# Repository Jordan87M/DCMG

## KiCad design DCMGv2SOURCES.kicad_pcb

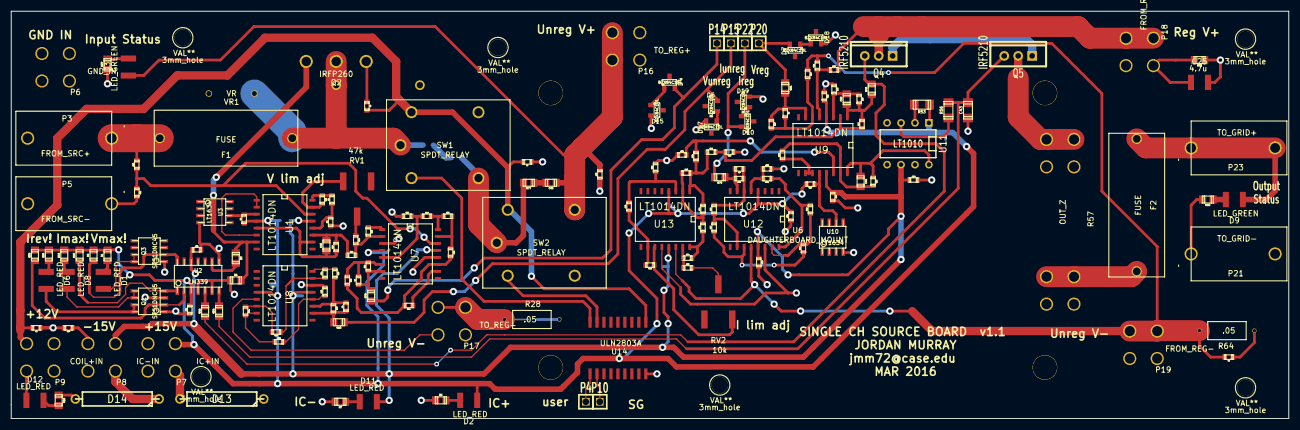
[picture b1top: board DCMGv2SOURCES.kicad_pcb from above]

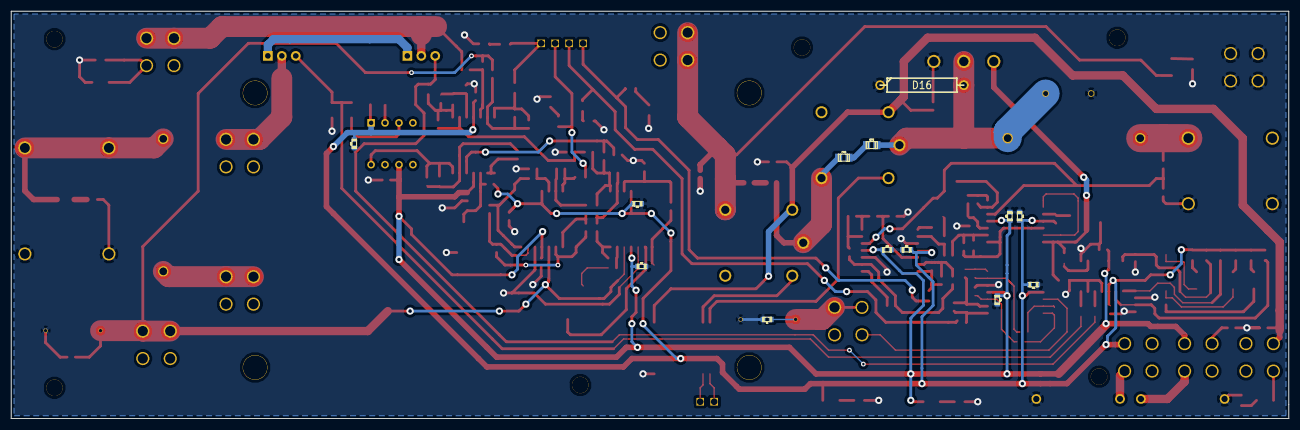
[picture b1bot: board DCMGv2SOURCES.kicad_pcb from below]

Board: 2 copper layers, 232.7 x 74.2 mm, 182 parts (13 on the bottom side), 102 nets.

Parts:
3mm_hole, 3mm_hole#2, 3mm_hole#3, 3mm_hole#4, 3mm_hole#5, 3mm_hole#6: VAL**; 3mm_hole
C1, C2: 10n; c_0603
C3, C4, C5, C9, C10: 2.2n; c_0603
C6, C7, C8: COIL_BYPASS; c_0603
C15, C33, C44: .22u; c_0805
C16: 1u; c_0603
C17, C18, C19, C20, C21, C22, C23, C24, C34, C35, C36, C37, C38, C39, C40, C41, C42: VCC_BYP; c_0603
C25: 4.7u; 1209
C43: 1.2u; c_1206
C45, C46: C; c_0805
D1, D2, D6, D8, D11, D12: LED_RED; 1209
D3, D9: LED_GREEN; 1209
D4, D5, D7, D10, D15, D17, D18, D19: BZX84C10L; SOT23
D13, D14, D16: DIODESCH; R6
F1, F2: FUSE; OMNI-BLOCK
P3: FROM_SRC+; DELTRON BANANA
P4: CTRL_SIG; MOLEX-1
P5: FROM_SRC-; DELTRON BANANA
P6: GND_IN; Screw Terminal 8191
P7: IC+IN; Screw Terminal 8191
P8: IC-IN; Screw Terminal 8191
P9: COIL+IN; Screw Terminal 8191
P10: NC_SCGR_SIG; MOLEX-1
P14: UNREG_V_SIG; MOLEX-1
P15: UNREG_I_SIG; MOLEX-1
P16: TO_REG+; Screw Terminal 8191
P17: TO_REG-; Screw Terminal 8191
P18: FROM_REG+; Screw Terminal 8191
P19: FROM_REG-; Screw Terminal 8191
P20: REG_V_SIG; MOLEX-1
P21: TO_GRID-; DELTRON BANANA
P22: REG_I_SIG; MOLEX-1
P23: TO_GRID+; DELTRON BANANA
Q1, Q3: STS1DNC45; so-8
Q2: IRFP260; TO247
Q4, Q5: IRF5210; TO220_VERT
R1, R6, R7, R10, R27, R36, R46, R62: 2.2k; c_0805
R2, R4, R39, R50: 33k; c_0805
R3, R44, R48, R54, R78, R79, R80, R81: 22; c_0805
R5, R43: 47k; c_0603
R8, R9, R11, R15, R16, R17, R19, R20, R22, R24, R25, R26, R37, R38, R41, R42, R47, R52, R55, R58: 12k; c_0603
R12: 10M; c_0603
R14, R21, R31, R34, R63, R67: 3.3k; c_0603
R18: 33k; c_0603
R23: 15k; c_0603
R28, R64: .05; OHMITE_1W
R29, R32, R61, R66, R70, R73: 5.6k; c_0603
R30, R33, R60, R65, R69, R72: 22k; c_0603
R35, R68, R75: 1.2k; c_0603
R40: MIN_LOAD; c_0805
R45, R49, R51, R59: 470; c_0603
R53: 50; c_1206
R56: 33; c_1206
R57: OUT_Z; Double Terminal 8191
R71, R74: 8.2k; c_0603
R76, R77: R; c_0805
RV1: 47k; Bourns_3361
RV2: 10k; Bourns_3361
SW1, SW2: SPDT_RELAY; OMRON_GL5E-1
U1, U7, U8, U9, U12, U13: LT1014DN; SO16W
U2: LM339; so-14
U3, U10: LT1634; so-8
U6: DAUGHTERBOARD_MOUNT
U11: LT1010; DIP-8__300
U14: ULN2803A; SOIC-18
VR1: VR; MOV-10DxxxK

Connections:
COIL_POW+: C6.1, C7.1, C8.1, D12.1, P9.1, SW1.2, SW2.2, U14.10
CTRL_GND: C1.1, C2.2, C6.2, C7.2, C8.2, C16.2, C17.1, C18.2, C19.1, C20.2, C21.1, C22.2, C23.1, C24.2, C25.2, C34.1, C35.2, C36.1, C37.2, C38.1, C39.2, C40.1, C41.2, C42.1, C43.2, D13.1, D14.2, D15.2, D16.1, D17.2, D18.2, D19.2, P5.1, P6.1, P21.1, Q1.1, Q1.3, Q2.3, Q3.1, R4.2, R6.2, R7.1, R9.2, R10.2, R20.2, R21.1, R27.2, R28.1, R30.1, R40.2, R45.2, R52.2, R58.2, R60.1, R62.1, R64.2, R69.1, U2.4, U2.6, U2.8, U3.4, U7.3, U7.12, U8.14, U10.4, U12.14, U13.12, U14.9, VR1.2
IC_POW+: C18.1, C20.1, C22.1, C24.1, C35.1, C37.1, C39.1, C41.1, D2.1, D13.2, P7.1, R1.1, R2.1, R5.2, R36.1, R39.1, R43.1, R46.1, R50.1, R53.2, U1.4, U2.3, U7.4, U8.4, U9.4, U11.1, U12.4, U13.4
IC_POW-: C17.2, C19.2, C21.2, C23.2, C34.2, C36.2, C38.2, C40.2, C42.2, D11.2, D14.1, P8.1, U1.13, U2.12, U7.13, U8.13, U9.13, U11.6, U12.13, U13.13
unnamed: R19.2, R20.1, U7.5
unnamed: C3.2, R26.2, R78.1, U7.7
unnamed: R22.1, R23.2, U7.15
unnamed: R24.2, U7.10
unnamed: R8.2, R9.1, U1.12
unnamed: C15.1, R16.2, R17.1, U1.11
unnamed: C15.2, R17.2, U1.5, U1.10
unnamed: R18.2, R21.2, U1.14, U7.14
unnamed: R15.2, U7.1
unnamed: R14.2, RV1.2
unnamed: Q1.2, R39.2, U2.2
unnamed: D8.1, R46.2
unnamed: D8.2, Q1.5, Q1.6
unnamed: R54.1, U2.7
unnamed: Q1.4, R50.2, U2.1
unnamed: R3.1, U2.9
unnamed: D6.1, R36.2
unnamed: D6.2, Q1.7, Q1.8
unnamed: R44.1, U2.5
unnamed: D3.2, R27.1
unnamed: C9.2, R65.2, R66.1, U12.6
unnamed: Q3.2, R2.2, U2.14
unnamed: D1.2, Q3.7, Q3.8
unnamed: SW2.9, U14.17
unnamed: P10.1, U14.2
unnamed: SW1.9, U14.18
unnamed: P4.1, U14.1
unnamed: C33.1, R45.1, R47.2, U9.3
unnamed: C33.2, R12.1, R47.1, R48.2, U9.1
unnamed: Q4.2, R44.2, R48.1
unnamed: D4.2, P14.1, R78.2
unnamed: D10.2, P22.1, R79.1
unnamed: D7.2, P20.1, R81.2
unnamed: D5.2, P15.1, R80.2
unnamed: C45.1, R76.2
unnamed: C45.2, R77.1, SW1.10, SW2.5
unnamed: C46.1, R77.2
unnamed: R75.1, RV2.2
unnamed: R69.2, R70.1, U13.3
unnamed: R49.2, U9.10, U9.11
unnamed: R43.2, U9.12, U10.6
unnamed: R12.2, R51.1, R52.1, U9.2
unnamed: R5.1, U1.3, U3.6
unnamed: U1.1, U1.2, U1.6
unnamed: R41.2, R42.2, U9.5
unnamed: D9.2, R62.2
unnamed: Q2.1, R3.2, R4.1, U1.7
unnamed: C44.2, R55.2, U9.16, U11.8
unnamed: C25.1, P18.1, Q4.3, R40.1, R42.1
unnamed: C5.2, R38.2, R81.1, U9.7
unnamed: C5.1, R37.1, R38.1, U9.6
unnamed: C9.1, R65.1, R79.2, U12.7
unnamed: C10.1, R51.2, R59.2, R72.1, U13.1
unnamed: C10.2, R72.2, R73.1, U13.2
unnamed: C3.1, R25.2, R26.1, U7.6
unnamed: C4.2, R33.1, R80.1, U8.10
unnamed: Q5.3, R57.2
unnamed: Q4.1, Q5.1
unnamed: D4.1, D15.1
unnamed: D5.1, D17.1
unnamed: D7.1, D18.1
unnamed: D10.1, D19.1
unnamed: R58.1, R59.1, U9.14
unnamed: C44.1, R49.1, R55.1, U9.15
unnamed: D1.1, R1.2
unnamed: C4.1, R32.1, R33.2, U8.11
unnamed: R29.1, R30.2, U8.12
unnamed: R53.1, U11.2
unnamed: R56.2, U11.3
unnamed: C43.1, Q5.2, R54.2, R56.1
unnamed: R60.2, R61.1, U12.5
unnamed: F2.2, R57.1
unnamed: D9.1, F2.1, P23.1
unnamed: R63.2, R68.1, U12.15
unnamed: R29.2, R31.1, U8.7
unnamed: R31.2, R35.1, U8.6
unnamed: R34.2, R35.2, U8.15
unnamed: R32.2, R34.1, U8.16
unnamed: R61.2, R63.1, U12.16
unnamed: R67.2, R68.2, U12.11
unnamed: R66.2, R67.1, U12.10
unnamed: C16.1, C46.2, D3.1, P16.1, SW2.1
unnamed: D11.1, R7.2
unnamed: D12.2, R10.1
unnamed: D2.2, R6.1
unnamed: C1.2, P17.1, R28.2, U8.5
unnamed: D16.2, F1.1, Q2.2, R76.1, SW1.5, VR1.1
unnamed: F1.2, P3.1, R18.1
unnamed: C2.1, P19.1, R37.2, R41.1, R64.1, U12.12, U13.14
unnamed: R19.1, R22.2, U7.16
unnamed: R23.1, R24.1, R25.1, U7.11
unnamed: R71.2, RV2.3, U13.11
unnamed: R70.2, R71.1, U13.10
unnamed: R74.2, R75.2, U13.15
unnamed: R73.2, R74.1, U13.16
unnamed: R14.1, R15.1, R16.1, U7.2
unnamed: R8.1, R11.2, U1.16
unnamed: R11.1, RV1.3, U1.15

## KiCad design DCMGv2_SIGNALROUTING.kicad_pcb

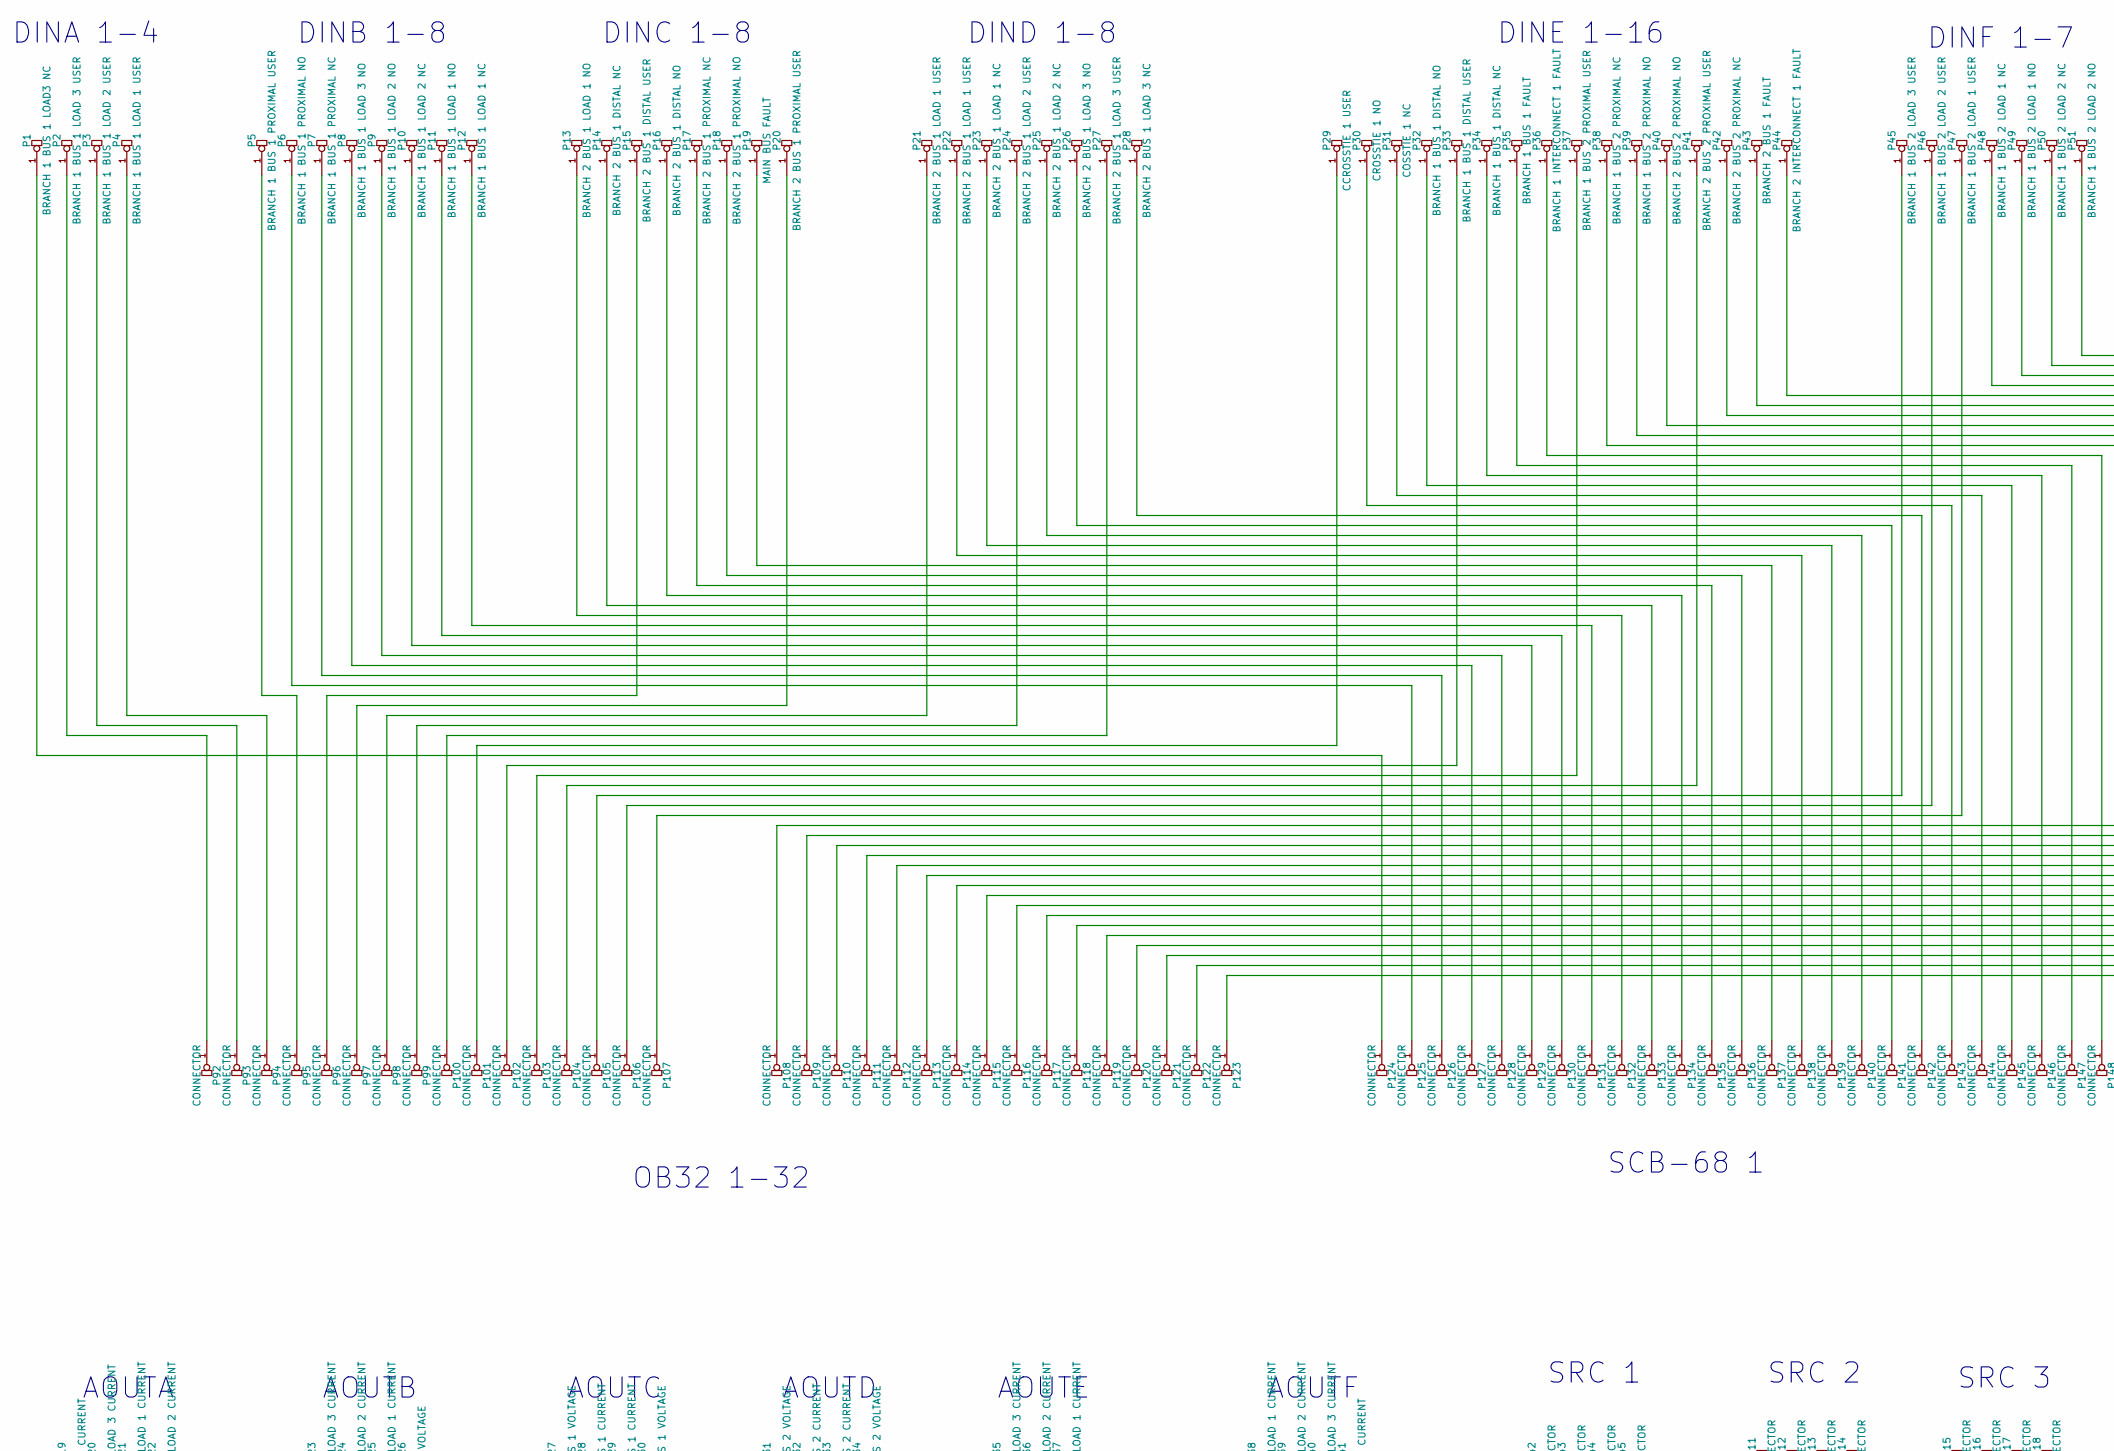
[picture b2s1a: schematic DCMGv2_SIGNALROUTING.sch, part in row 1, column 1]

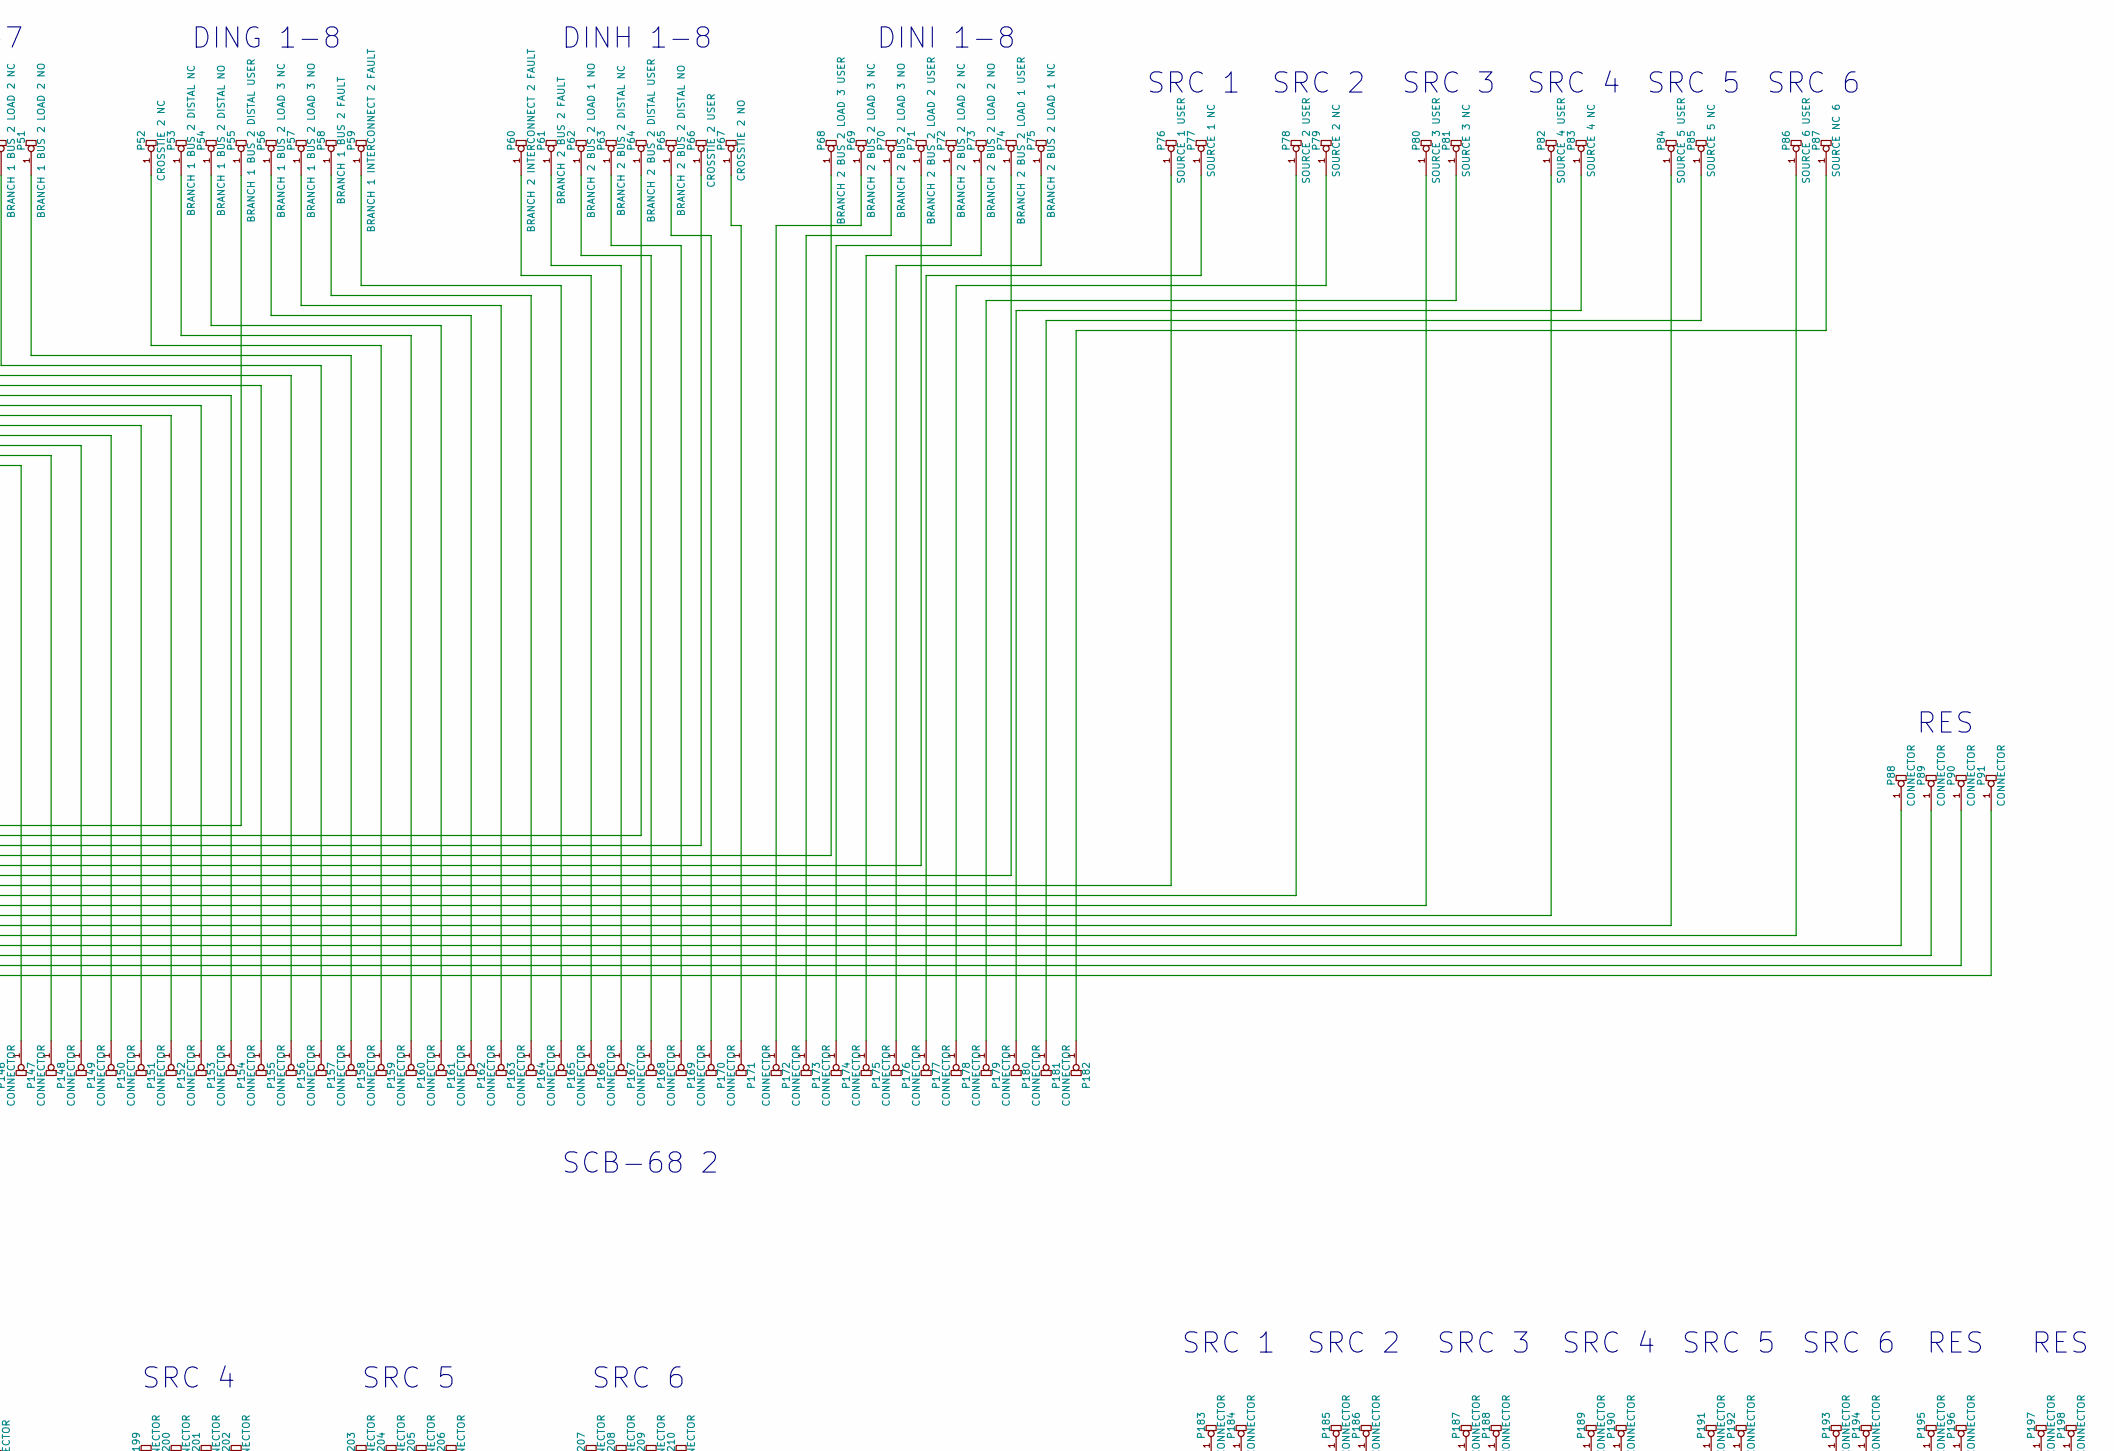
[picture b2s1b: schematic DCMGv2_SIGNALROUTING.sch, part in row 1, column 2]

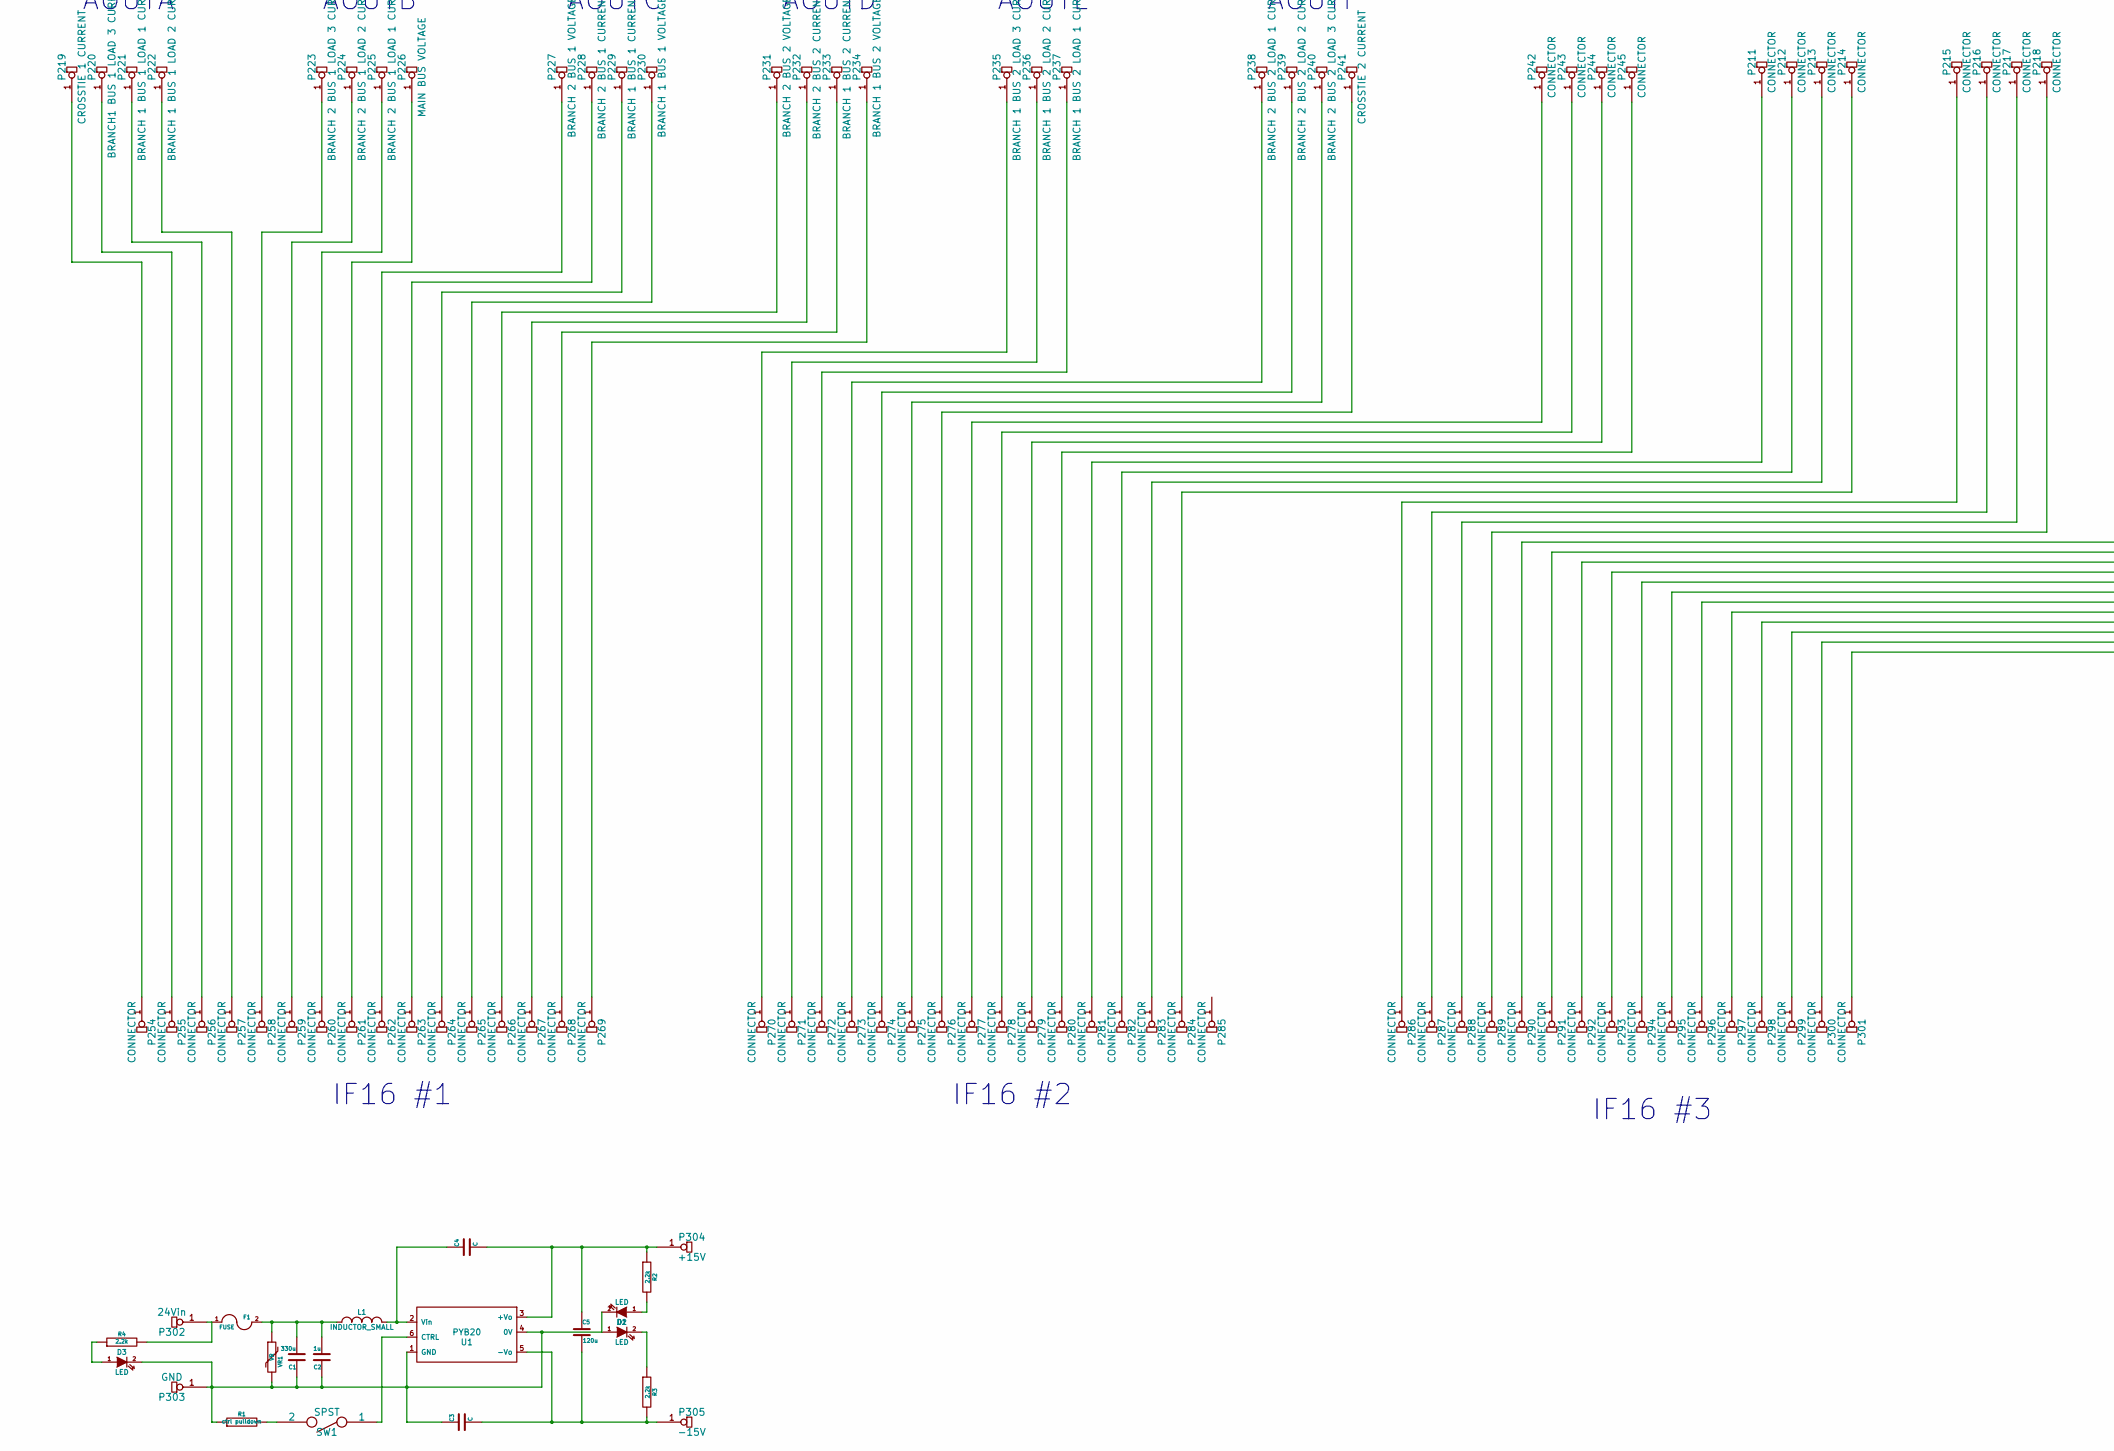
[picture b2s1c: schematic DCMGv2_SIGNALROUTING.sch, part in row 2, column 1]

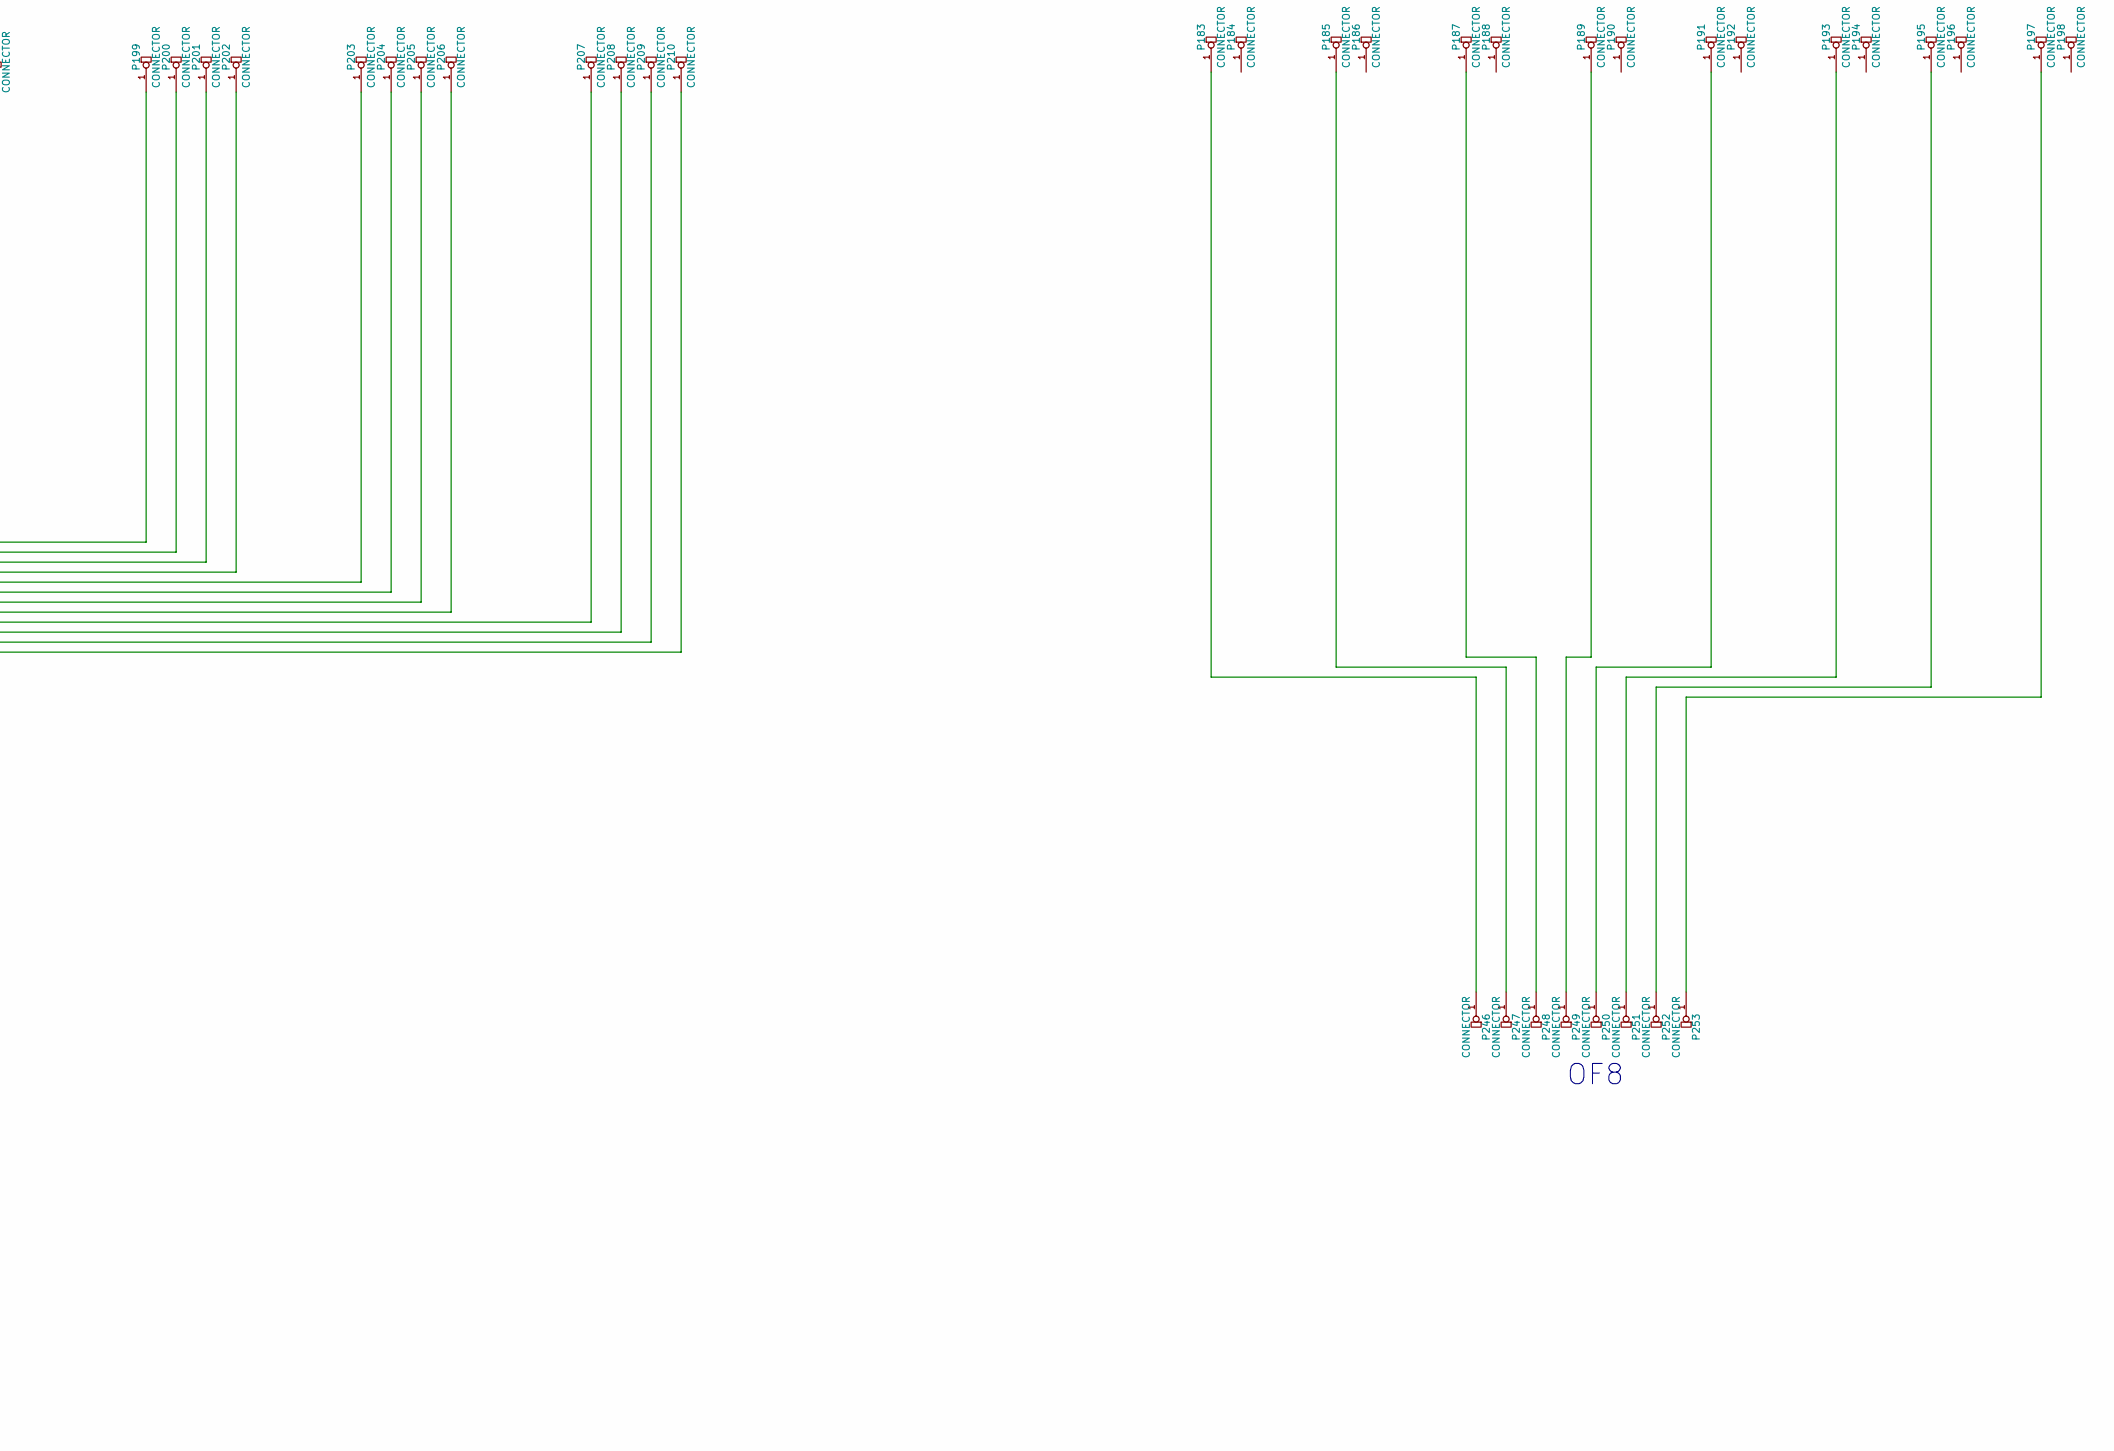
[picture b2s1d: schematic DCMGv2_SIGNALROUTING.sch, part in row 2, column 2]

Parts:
C1: 330u
C2: 1u
C3, C4: C
C5: 120u
D1, D2, D3: LED
F1: FUSE
L1: INDUCTOR_SMALL
P1: BRANCH 1 BUS 1 LOAD3 NC
P2: BRANCH 1 BUS 1 LOAD 3 USER
P3: BRANCH 1 BUS 1 LOAD 2 USER
P4: BRANCH 1 BUS 1 LOAD 1 USER
P5: BRANCH 1 BUS 1 PROXIMAL USER
P6: BRANCH 1 BUS 1 PROXIMAL NO
P7: BRANCH 1 BUS 1 PROXIMAL NC
P8: BRANCH 1 BUS 1 LOAD 3 NO
P9: BRANCH 1 BUS 1 LOAD 2 NO
P10: BRANCH 1 BUS 1 LOAD 2 NC
P11: BRANCH 1 BUS 1 LOAD 1 NO
P12: BRANCH 1 BUS 1 LOAD 1 NC
P13: BRANCH 2 BUS 1 LOAD 1 NO
P14: BRANCH 2 BUS 1 DISTAL NC
P15: BRANCH 2 BUS 1 DISTAL USER
P16: BRANCH 2 BUS 1 DISTAL NO
P17: BRANCH 2 BUS 1 PROXIMAL NC
P18: BRANCH 2 BUS 1 PROXIMAL NO
P19: MAIN BUS FAULT
P20: BRANCH 2 BUS 1 PROXIMAL USER
P21, P22: BRANCH 2 BUS 1 LOAD 1 USER
P23: BRANCH 2 BUS 1 LOAD 1 NC
P24: BRANCH 2 BUS 1 LOAD 2 USER
P25: BRANCH 2 BUS 1 LOAD 2 NC
P26: BRANCH 2 BUS 1 LOAD 3 NO
P27: BRANCH 2 BUS 1 LOAD 3 USER
P28: BRANCH 2 BUS 1 LOAD 3 NC
P29: CCROSSTIE 1 USER
P30: CROSSTIE 1 NO
P31: COSSTIE 1 NC
P32: BRANCH 1 BUS 1 DISTAL NO
P33: BRANCH 1 BUS 1 DISTAL USER
P34: BRANCH 1 BUS 1 DISTAL NC
P35: BRANCH 1 BUS 1 FAULT
P36: BRANCH 1 INTERCONNECT 1 FAULT
P37: BRANCH 1 BUS 2 PROXIMAL USER
P38: BRANCH 1 BUS 2 PROXIMAL NC
P39: BRANCH 1 BUS 2 PROXIMAL NO
P40: BRANCH 2 BUS 2 PROXIMAL NO
P41: BRANCH 2 BUS 2 PROXIMAL USER
P42: BRANCH 2 BUS 2 PROXIMAL NC
P43: BRANCH 2 BUS 1 FAULT
P44: BRANCH 2 INTERCONNECT 1 FAULT
P45: BRANCH 1 BUS 2 LOAD 3 USER
P46: BRANCH 1 BUS 2 LOAD 2 USER
P47: BRANCH 1 BUS 2 LOAD 1 USER
P48: BRANCH 1 BUS 2 LOAD 1 NC
P49: BRANCH 1 BUS 2 LOAD 1 NO
P50: BRANCH 1 BUS 2 LOAD 2 NC
P51: BRANCH 1 BUS 2 LOAD 2 NO
P52: CROSSTIE 2 NC
P53: BRANCH 1 BUS 2 DISTAL NC
P54: BRANCH 1 BUS 2 DISTAL NO
P55: BRANCH 1 BUS 2 DISTAL USER
P56: BRANCH 1 BUS 2 LOAD 3 NC
P57: BRANCH 1 BUS 2 LOAD 3 NO
P58: BRANCH 1 BUS 2 FAULT
P59: BRANCH 1 INTERCONNECT 2 FAULT
P60: BRANCH 2 INTERCONNECT 2 FAULT
P61: BRANCH 2 BUS 2 FAULT
P62: BRANCH 2 BUS 2 LOAD 1 NO
P63: BRANCH 2 BUS 2 DISTAL NC
P64: BRANCH 2 BUS 2 DISTAL USER
P65: BRANCH 2 BUS 2 DISTAL NO
P66: CROSSTIE 2 USER
P67: CROSSTIE 2 NO
P68: BRANCH 2 BUS 2 LOAD 3 USER
P69: BRANCH 2 BUS 2 LOAD 3 NC
P70: BRANCH 2 BUS 2 LOAD 3 NO
P71: BRANCH 2 BUS 2 LOAD 2 USER
P72: BRANCH 2 BUS 2 LOAD 2 NC
P73: BRANCH 2 BUS 2 LOAD 2 NO
P74: BRANCH 2 BUS 2 LOAD 1 USER
P75: BRANCH 2 BUS 2 LOAD 1 NC
P76: SOURCE 1 USER
P77: SOURCE 1 NC
P78: SOURCE 2 USER
P79: SOURCE 2 NC
P80: SOURCE 3 USER
P81: SOURCE 3 NC
P82: SOURCE 4 USER
P83: SOURCE 4 NC
P84: SOURCE 5 USER
P85: SOURCE 5 NC
P86: SOURCE 6 USER
P87: SOURCE NC 6
P88, P89, P90, P91, P92, P93, P94, P95, P96, P97, P98, P99, P100, P101, P102, P103, P104, P105, P106, P107, P108, P109, P110, P111, P112, P113, P114, P115, P116, P117, P118, P119, P120, P121, P122, P123, P124, P125, P126, P127, P128, P129, P130, P131, P132, P133, P134, P135, P136, P137, P138, P139, P140, P141, P142, P143, P144, P145, P146, P147, P148, P149, P150, P151, P152, P153, P154, P155, P156, P157, P158, P159, P160, P161, P162, P163, P164, P165, P166, P167, P168, P169, P170, P171, P172, P173, P174, P175, P176, P177, P178, P179, P180, P181, P182, P183, P184, P185, P186, P187, P188, P189, P190, P191, P192, P193, P194, P195, P196, P197, P198, P199, P200, P201, P202, P203, P204, P205, P206, P207, P208, P209, P210, P211, P212, P213, P214, P215, P216, P217, P218, P242, P243, P244, P245, P246, P247, P248, P249, P250, P251, P252, P253, P254, P255, P256, P257, P258, P259, P260, P261, P262, P263, P264, P265, P266, P267, P268, P269, P270, P271, P272, P273, P274, P275, P276, P277, P278, P279, P280, P281, P282, P283, P284, P285, P286, P287, P288, P289, P290, P291, P292, P293, P294, P295, P296, P297, P298, P299, P300, P301: CONNECTOR
P219: CROSSTIE 1 CURRENT
P220: BRANCH1 BUS 1 LOAD 3 CURRENT
P221: BRANCH 1 BUS 1 LOAD 1 CURRENT
P222: BRANCH 1 BUS 1 LOAD 2 CURRENT
P223: BRANCH 2 BUS 1 LOAD 3 CURRENT
P224: BRANCH 2 BUS 1 LOAD 2 CURRENT
P225: BRANCH 2 BUS 1 LOAD 1 CURRENT
P226: MAIN BUS VOLTAGE
P227: BRANCH 2 BUS 1 VOLTAGE
P228: BRANCH 2 BUS 1 CURRENT
P229: BRANCH 1 BUS 1 CURRENT
P230: BRANCH 1 BUS 1 VOLTAGE
P231: BRANCH 2 BUS 2 VOLTAGE
P232: BRANCH 2 BUS 2 CURRENT
P233: BRANCH 1 BUS 2 CURRENT
P234: BRANCH 1 BUS 2 VOLTAGE
P235: BRANCH 1 BUS 2 LOAD 3 CURRENT
P236: BRANCH 1 BUS 2 LOAD 2 CURRENT
P237: BRANCH 1 BUS 2 LOAD 1 CURRENT
P238: BRANCH 2 BUS 2 LOAD 1 CURRENT
P239: BRANCH 2 BUS 2 LOAD 2 CURRENT
P240: BRANCH 2 BUS 2 LOAD 3 CURRENT
P241: CROSSTIE 2 CURRENT
P302: 24Vin
P303: GND
P304: +15V
P305: -15V
R1: ctrl pulldown
R2, R3, R4: 2.2k
SW1: SPST
U1: PYB20
VR1: VR

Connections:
unnamed: P225.1, P260.1
unnamed: P220.1, P255.1
unnamed: P221.1, P256.1
unnamed: P222.1, P257.1
unnamed: P223.1, P258.1
unnamed: P224.1, P259.1
unnamed: P226.1, P261.1
unnamed: P227.1, P262.1
unnamed: P228.1, P263.1
unnamed: P229.1, P264.1
unnamed: P79.1, P178.1
unnamed: P80.1, P116.1
unnamed: P82.1, P117.1
unnamed: P84.1, P118.1
unnamed: P86.1, P119.1
unnamed: P81.1, P179.1
unnamed: P83.1, P180.1
unnamed: P219.1, P254.1
unnamed: P242.1, P277.1
unnamed: P238.1, P273.1
unnamed: P239.1, P274.1
unnamed: P240.1, P275.1
unnamed: P241.1, P276.1
unnamed: P243.1, P278.1
unnamed: P244.1, P279.1
unnamed: P245.1, P280.1
unnamed: P211.1, P281.1
unnamed: P230.1, P265.1
unnamed: P231.1, P266.1
unnamed: P232.1, P267.1
unnamed: P233.1, P268.1
unnamed: P234.1, P269.1
unnamed: P235.1, P270.1
unnamed: P236.1, P271.1
unnamed: P237.1, P272.1
unnamed: P57.1, P163.1
unnamed: P53.1, P160.1
unnamed: P54.1, P161.1
unnamed: P55.1, P108.1
unnamed: P56.1, P162.1
unnamed: P58.1, P164.1
unnamed: P59.1, P165.1
unnamed: P60.1, P166.1
unnamed: P61.1, P167.1
unnamed: P48.1, P155.1
unnamed: P44.1, P154.1
unnamed: P45.1, P105.1
unnamed: P46.1, P106.1
unnamed: P47.1, P107.1
unnamed: P49.1, P156.1
unnamed: P50.1, P157.1
unnamed: P51.1, P158.1
unnamed: P52.1, P159.1
unnamed: P70.1, P173.1
unnamed: P71.1, P112.1
unnamed: P72.1, P174.1
unnamed: P73.1, P175.1
unnamed: P74.1, P113.1
unnamed: P75.1, P176.1
unnamed: P76.1, P114.1
unnamed: P77.1, P177.1
unnamed: P78.1, P115.1
unnamed: P65.1, P170.1
unnamed: P62.1, P168.1
unnamed: P63.1, P169.1
unnamed: P64.1, P109.1
unnamed: P66.1, P110.1
unnamed: P67.1, P171.1
unnamed: P68.1, P111.1
unnamed: P69.1, P172.1
unnamed: C1.2, C2.2, F1.2, L1.1, VR1.1
unnamed: P91.1, P123.1
unnamed: SW1.1, U1.6 (CTRL)
unnamed: C4.1, L1.2, U1.2 (Vin)
unnamed: C3.2, C5.2, P305.1, R3.2, U1.5 (-Vo)
unnamed: R1.2, SW1.2
unnamed: D3.1 (A), R4.1
unnamed: F1.1, P302.1, R4.2
unnamed: C1.1, C2.1, C3.1, D1.2 (K), D2.1 (A), D3.2 (K), P303.1, R1.1, U1.1 (GND), U1.4 (0V), VR1.2
unnamed: C4.2, C5.1, P304.1, R2.1, U1.3 (+Vo)
unnamed: D1.1 (A), R2.2
unnamed: D2.2 (K), R3.1
unnamed: P205.1, P296.1
unnamed: P200.1, P291.1
unnamed: P201.1, P292.1
unnamed: P202.1, P293.1
unnamed: P203.1, P294.1
unnamed: P204.1, P295.1
unnamed: P206.1, P297.1
unnamed: P85.1, P181.1
unnamed: P87.1, P182.1
unnamed: P216.1, P287.1
unnamed: P212.1, P282.1
unnamed: P213.1, P283.1
unnamed: P214.1, P284.1
unnamed: P215.1, P286.1
unnamed: P183.1, P246.1
unnamed: P217.1, P288.1
unnamed: P218.1, P289.1
unnamed: P199.1, P290.1
unnamed: P210.1, P301.1
unnamed: P209.1, P300.1
unnamed: P207.1, P298.1
unnamed: P208.1, P299.1
unnamed: P88.1, P120.1
unnamed: P90.1, P122.1
unnamed: P89.1, P121.1
unnamed: P185.1, P247.1
unnamed: P187.1, P248.1
unnamed: P197.1, P253.1
unnamed: P189.1, P249.1
unnamed: P191.1, P250.1
unnamed: P193.1, P251.1
unnamed: P195.1, P252.1
unnamed: P31.1, P144.1
unnamed: P25.1, P140.1
unnamed: P12.1, P131.1
unnamed: P10.1, P129.1
unnamed: P8.1, P127.1
unnamed: P6.1, P125.1
unnamed: P1.1, P124.1
unnamed: P39.1, P150.1
unnamed: P41.1, P104.1
unnamed: P28.1, P142.1
unnamed: P29.1, P101.1
unnamed: P30.1, P143.1
unnamed: P32.1, P145.1
unnamed: P33.1, P102.1
unnamed: P34.1, P146.1
unnamed: P35.1, P147.1
unnamed: P36.1, P148.1
unnamed: P37.1, P103.1
unnamed: P38.1, P149.1
unnamed: P40.1, P151.1
unnamed: P27.1, P100.1
unnamed: P42.1, P152.1
unnamed: P43.1, P153.1
unnamed: P14.1, P133.1
unnamed: P7.1, P126.1
unnamed: P11.1, P130.1
unnamed: P16.1, P134.1
unnamed: P17.1, P135.1
unnamed: P19.1, P137.1
unnamed: P20.1, P97.1
unnamed: P21.1, P98.1
unnamed: P24.1, P99.1
unnamed: P26.1, P141.1
unnamed: P4.1, P94.1
unnamed: P3.1, P93.1
unnamed: P2.1, P92.1
unnamed: P5.1, P95.1
unnamed: P23.1, P139.1
unnamed: P18.1, P136.1
unnamed: P15.1, P96.1
unnamed: P22.1, P138.1
unnamed: P13.1, P132.1
unnamed: P9.1, P128.1

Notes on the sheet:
DINA 1-4
DINB 1-8
DINC 1-8
DIND 1-8
DINE 1-16
DINF 1-7
DING 1-8
DINH 1-8
DINI 1-8
SCB-68 1
SRC 1
SRC 2
SRC 3
SRC 4
SRC 5
SRC 6
IF16 #1
IF16 #2
IF16 #3
OF8
OB32 1-32
SCB-68 2
AOUTA
AOUTB
AOUTC
AOUTD
AOUTE
AOUTF
RES
